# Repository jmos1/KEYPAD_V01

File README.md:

# KEYPAD_V01

### Summary: ###
  This is a 3x3 keypad designed around the budget STMF103 Cortex-M3 series of microcontrollers. 
  It interfaces to the PC with a USB micro B connector and can be programmed through the SWD interface adjacent to it.

  The BOM, schematic PDF, and gerber files are all accessible in the _'Outputs/'_ folder. 
  Other project files are not included because they add clutter and can be generated from the project itself in KiCad.
  Thanks.

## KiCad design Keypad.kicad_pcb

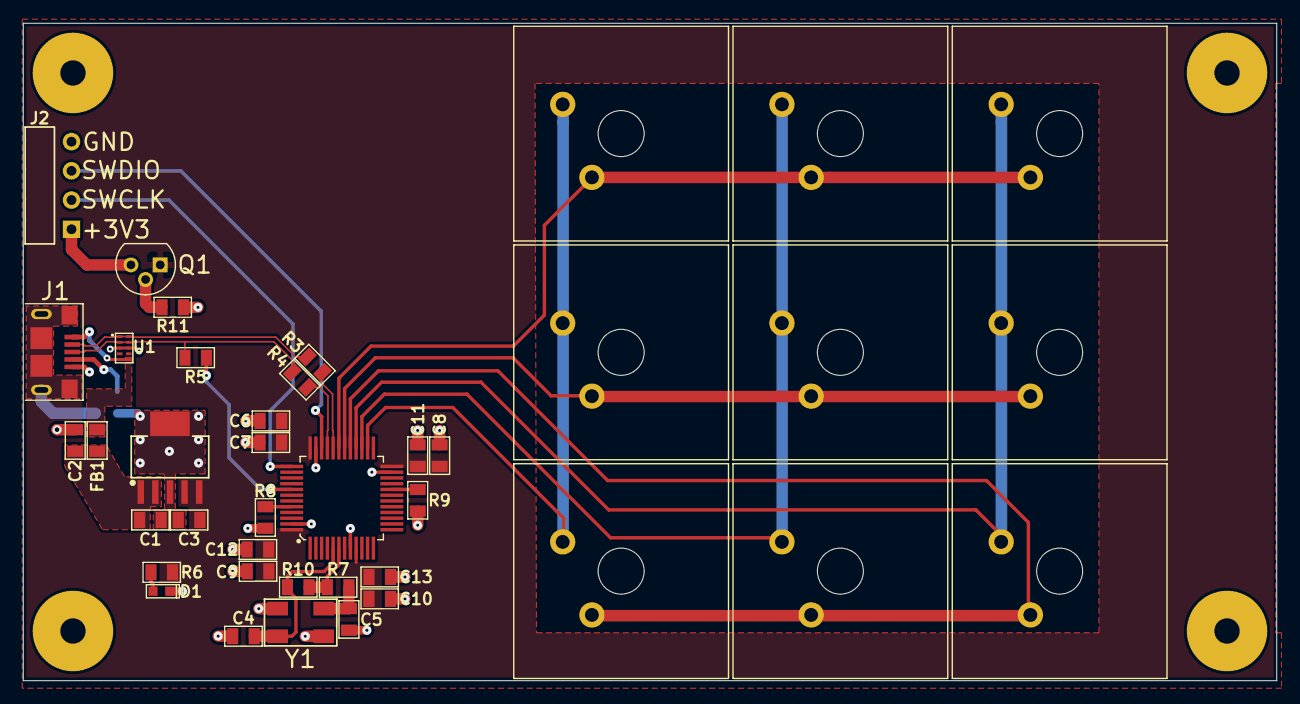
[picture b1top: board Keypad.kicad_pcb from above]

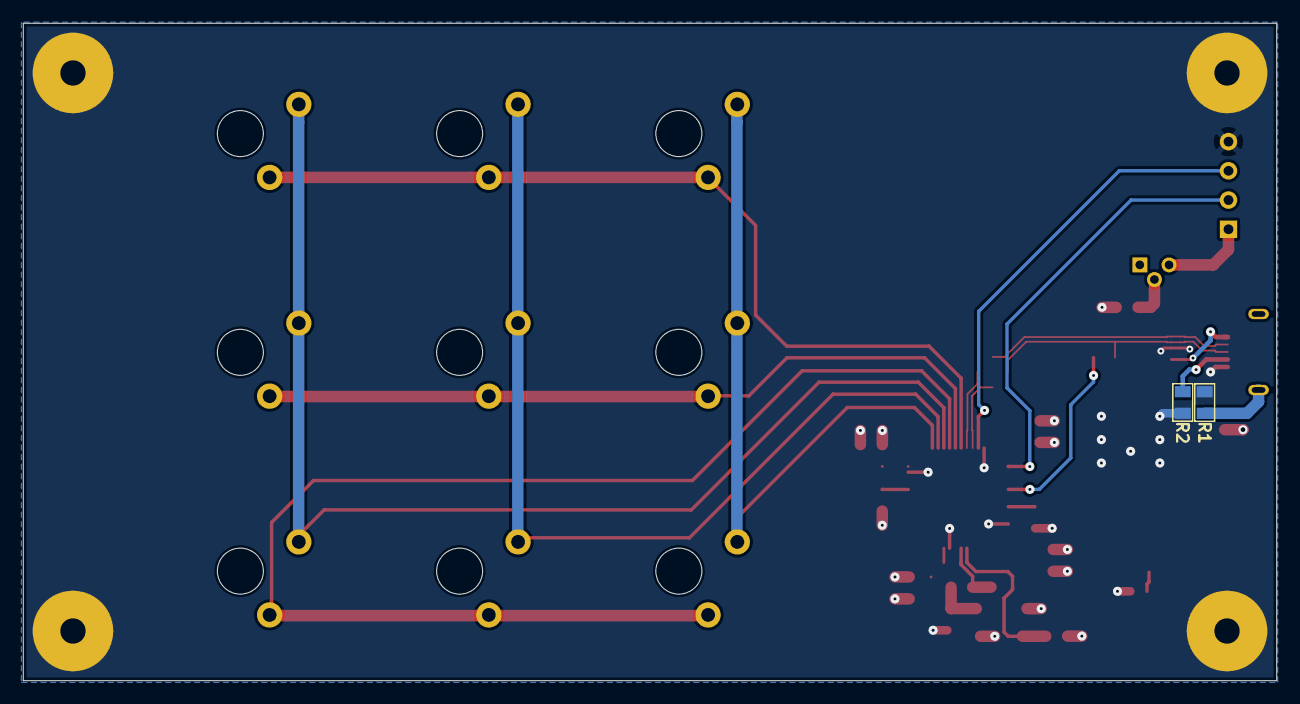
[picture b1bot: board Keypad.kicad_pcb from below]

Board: 2 copper layers, 109.0 x 57.2 mm, 46 parts (2 on the bottom side), 27 nets.

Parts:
C1, C3: CGA4J1X5R1C106M125AC; C0805
C2, C6, C8, C9, C10: CGA4J3X7R1E105K125AB; C0805
C4, C5: C0805C100J3GAC7800; C0805
C7, C11, C12, C13: C2012X7R1H104K085AA; C0805
D1: L29K-F2J1-24-Z; LG L29K-F2J1-24-Z
FB1: MPZ2012S601AT000; C0805
H1, H2, H3, H4: MOUNTING_HOLE_2.2MM_M2; MountingHole_2.2MM_M2_PAD
J1: 10118193-0001LF; FCI_10118193-0001LF
J2: M20-9750446; HDR_MALE_RA_2.54MM_1X4
Q1: BC32725TA; TO-92
R1, R2, R7: RC0805JR-070RL; R0805
R3, R4: AC0805FR-0722RL; R0805
R5: CRG0805F1K5; R0805
R6, R11: RC0805FR-07560RL; R0805
R8, R9: RC0805FR-0710KL; R0805
R10: RC0805FR-071ML; R0805
SW1, SW2, SW3, SW4, SW5, SW6, SW7, SW8, SW9: MX1A-11NN; SW_CherryMX_1U
U1: PUSB3FR4Z
U2: TL1963A-33DCQT
U3: STM32F103C8T6TR; LQFP-48_STM32F103
Y1: ABM3B-8.000MHZ-10-D-1-G-T; NX8045GB-8.000000MHZ

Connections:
+5V: C1.1, C2.1, FB1.2, U2.1, U2.2
/22R_D+: J1.3, R4.1, R5.1, U1.2, U1.9
/22R_D-: J1.2, R3.1, U1.1, U1.10
/BOOT0: R8.2, U3.44
/BOOT1: R9.2, U3.20
/OSC_IN: C4.2, R10.1, U3.5, Y1.3
/OSC_OUT: R7.2, R10.2, U3.6
/PNP_B: Q1.2, R11.2
/PNP_E: J2.1, Q1.3
/TVS_FB: FB1.1, J1.1, U1.5, U1.6
/USB_ID: J1.4, R2.1
GND: C1.2, C2.2, C3.1, C4.1, C5.1, C6.2, C7.2, C8.2, C9.2, C10.2, C11.2, C12.2, C13.2, D1.2, H1.1, H2.1, H3.1, H4.1, J1.5, J2.4, R1.2, R2.2, R8.1, R9.1, R11.1, U1.3, U1.8, U2.3, U2.6, U3.8, U3.23, U3.35, U3.47, Y1.2, Y1.4
unnamed: C5.2, R7.1, Y1.1
unnamed: D1.1, R6.2
unnamed: J1.S1, J1.S2, J1.S3, J1.S4, J1.S5, J1.S6, R1.1
PA8_OUT: SW1.2, SW2.2, SW3.2, U3.29
PA9_OUT: SW4.2, SW5.2, SW6.2, U3.30
PA10_OUT: SW7.2, SW8.2, SW9.2, U3.31
PB13_IN: SW1.1, SW4.1, SW7.1, U3.26
PB14_IN: SW2.1, SW5.1, SW8.1, U3.27
PB15_IN: SW3.1, SW6.1, SW9.1, U3.28
SWCLK: J2.2, U3.37
SWDIO: J2.3, U3.34
USBD+: R4.2, U3.33
USBD-: R3.2, U3.32
USBDP_PUP: R5.2, U3.41
VDDA: C3.2, C6.1, C7.1, C8.1, C9.1, C10.1, C11.1, C12.1, C13.1, Q1.1, R6.1, U2.4, U2.5, U3.9, U3.24, U3.36, U3.48

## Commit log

2020-06-15 Test Commit
2020-06-15 Initial big push
2020-06-15 Modified BOM
2020-06-15 Minor measurement fixes
2020-06-16 Modifications to schematic
2020-06-16 Modified layers picture
2020-06-24 Upadated schematic
